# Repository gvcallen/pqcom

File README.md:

# PocketQube Satellite Communication System

## Overview
This repository holds code, datasheets, PCB schematics and other files related to the design and development of a PocketQube Satellite Communication System. This was done by Gary Allen in  partial fulfilment of the requirements of the module Project (E) 448 for the degree Baccalaureus in Engineering in the Department of Electrical and Electronic Engineering at the University of Stellenbosch, South Africa. PocketQubes are miniaturised satellites, and this project aimed to develop prototypes for the unit to be placed on the satellite, the ground station, and the PC interface. A video documenting the project can be found on YouTube at https://www.youtube.com/watch?v=bJcF6t-W-kM

## Code
This folder contains the relevant code for the project. Inside are 5 sub-folders. All embedded development was done using the *PlatformIO* extension on VS code, and all desktop GUI development was done using the *Qt* C++ library, both under WSL (Windows Subsystem for Linux). I highly recommend a linux install due to the ease of installation of the Qt libraries.
- ***gel*** is another Github repository created by myself containing the core embedded C++ classes used by the other projects. Even though it was developed solely for this project, I decided to make it an independent library so that it can be self-standing and potentially be used outside of the PocketQube project in the future.
- ***pqcu*** is the folder housing the code for the *PocketQube Communication Unit* i.e. the module to be placed on the PQ itself. It is very simple since it only "spits out" its GPS location via LoRa (i.e only downlink communication was implemented) however "gel" theoretically has an almost-ready foundation for dual-link communication (which was not implemented due to time constraints).
- ***pqgs*** contains code for the *PocketQube Ground Station*. This includes communication with the PQ unit, motor drive control, GPS tracking and serial control via a "TNC" (a.k.a a laptop connected via USB).
- ***pqui*** contains desktop GUI code to control the GS via USB and a PC. Theoretically, all control can be done via the terminal, however the GUI was implemented to make things slightly easier. It implements the SUNCQ protocol under ***Documents***.
- ***radiosonde_auto_rx*** was an extension of the project to receive data from a commercial Radiosonde via a software-defined radio (SDR). This is used by ***pqui***. Although the Radiosonde receiving is functional, it is currently implemented is a bit "messy", since a Python script is called and controlled from Qt, and this causes issues from time-to-time. If only "custom" communication is needed, this can be ignored.

## Other
The rest of the contents are relatively self-explanatory:
- ***datasheets*** contains various used (and not used) datasheets for ICs and modules.
- ***documents*** contains the SUNCQ protocol for PC to GS communication.
- ***images*** contains images taken throughout the project, such as during testing and final deployment.
- ***kicad*** contains the schematics developed for the PQ and the GS. The final Gerber files are also present in zip format. Note that some folders in here are old and need to be cleaned up.
- ***link-budget*** contains a pre-liminary link-budget done with free Python software.
- ***report*** contains the final report files for Latex. The final PDF is in the root of this folder.
- ***testing*** contains test results and data.

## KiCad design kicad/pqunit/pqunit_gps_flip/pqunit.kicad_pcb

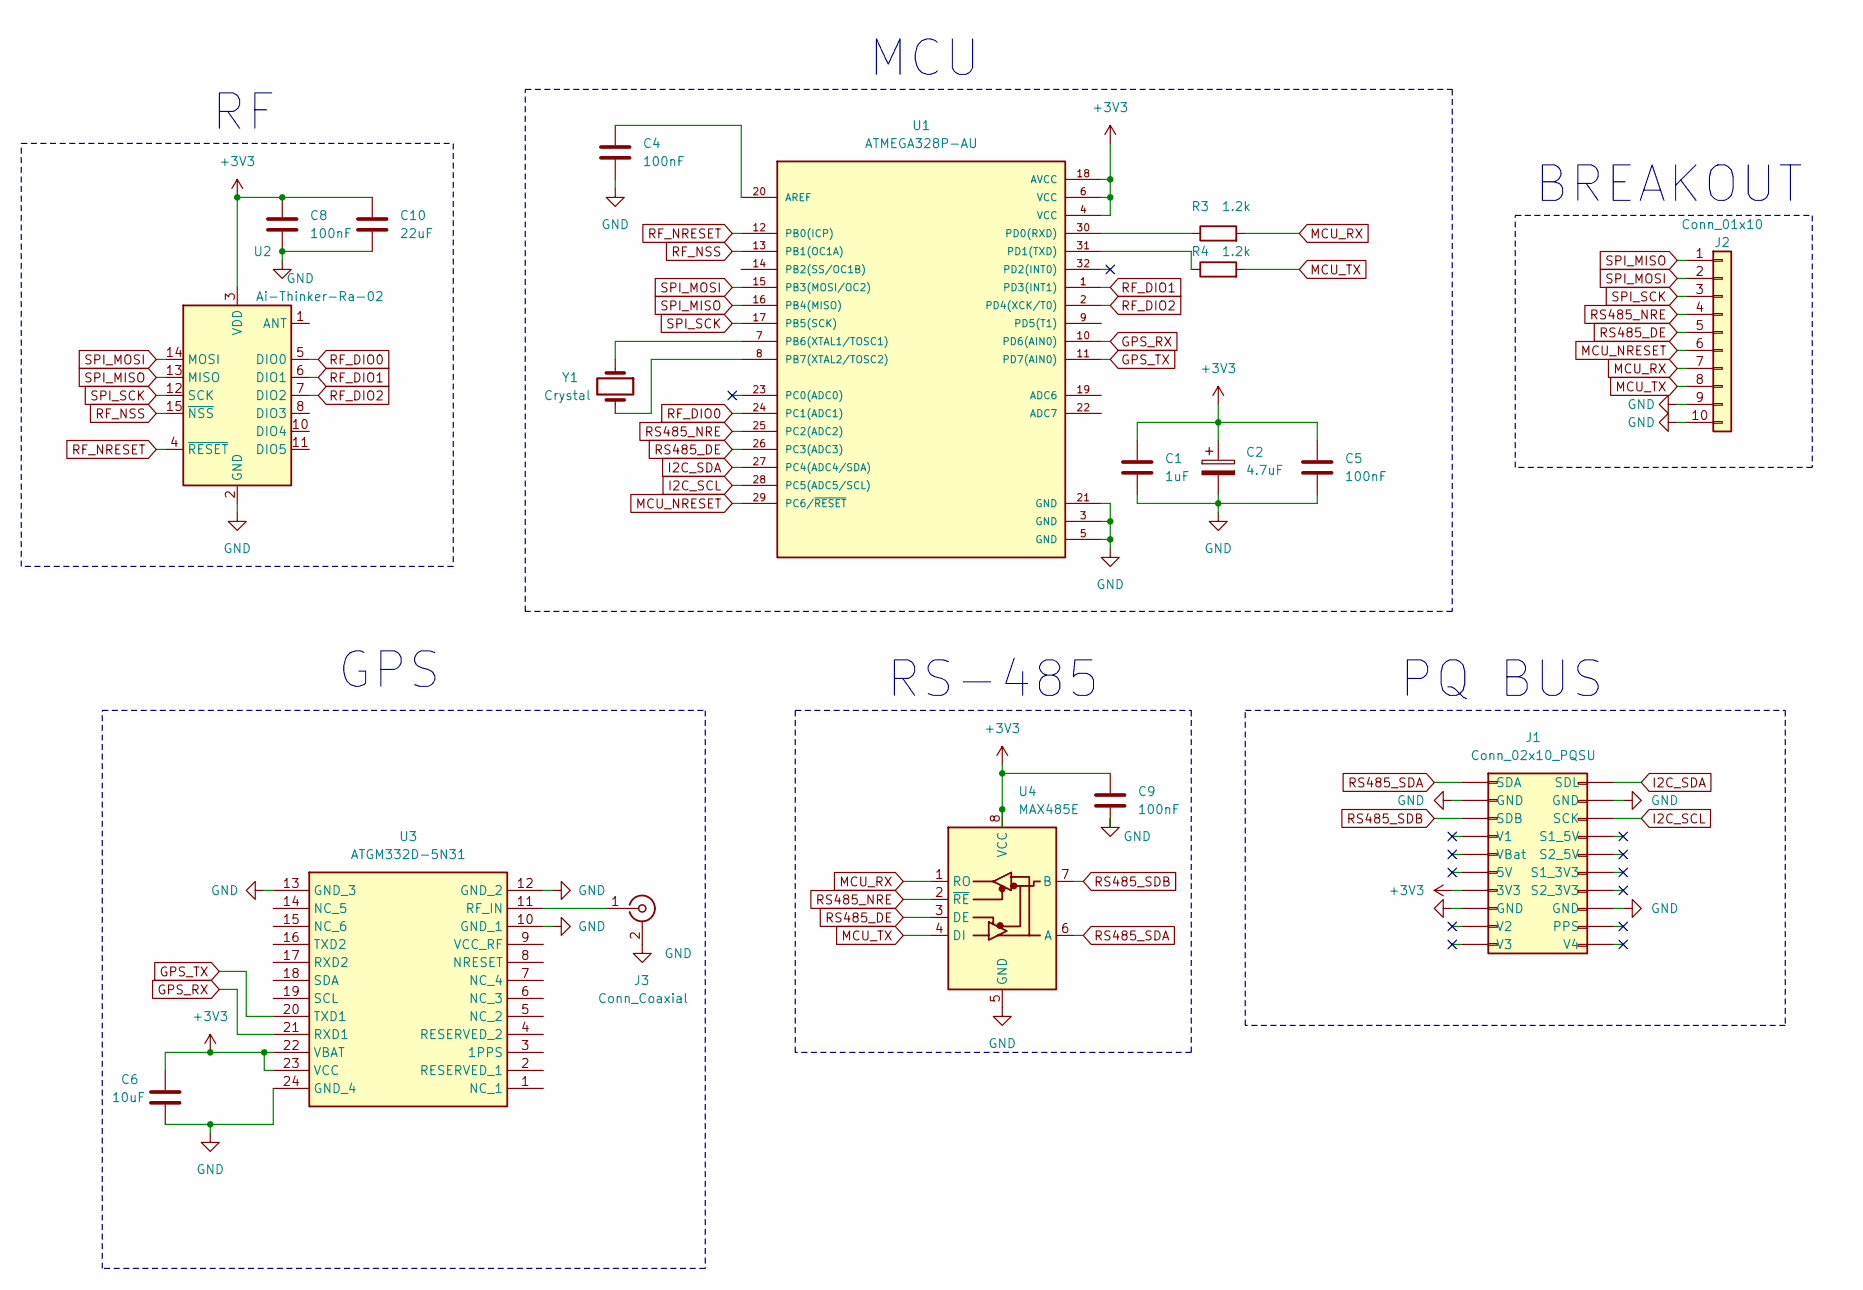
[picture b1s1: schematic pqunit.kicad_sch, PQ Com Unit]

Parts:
C1: 1uF; C_1206_3216Metric_Pad1.33x1.80mm_HandSolder
C2: 4.7uF; C_1206_3216Metric_Pad1.33x1.80mm_HandSolder
C4, C5, C8, C9: 100nF; C_0805_2012Metric_Pad1.18x1.45mm_HandSolder
C6: 10uF; C_1206_3216Metric_Pad1.33x1.80mm_HandSolder
C10: 22uF; C_1206_3216Metric_Pad1.33x1.80mm_HandSolder
J1: Conn_02x10_PQSU; PinSocket_2x10_P2.54mm_Vertical
J2: Conn_01x10; PinSocket_1x10_P2.54mm_Vertical
J3: Conn_Coaxial; U.FL_Molex_MCRF_73412-0110_Vertical
R3, R4: 1.2k; R_0805_2012Metric_Pad1.20x1.40mm_HandSolder
U1: ATMEGA328P-AU; TQFP-32_7x7mm_P0.8mm
U2: Ai-Thinker-Ra-02; Ai-Thinker-Ra-01-LoRa
U3: ATGM332D-5N31; ATGM332D5N31; Manufacturer_Part_Number ATGM332D-5N31
U4: MAX485E; SO08
Y1: Crystal; Crystal_SMD_HC49-SD

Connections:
+3V3: C1.1, C2.1, C5.1, C6.1, C8.1, C9.1, C10.1, J1.7 (3V3), U1.4 (VCC), U1.6 (VCC), U1.18 (AVCC), U2.3 (VDD), U3.22 (VBAT), U3.23 (VCC), U4.8 (VCC)
GND: C1.2, C2.2, C4.2, C5.2, C6.2, C8.2, C9.2, C10.2, J1.2 (GND), J1.8 (GND), J1.12 (GND), J1.18 (GND), J2.9, J2.10, J3.2 (Ext), U1.3 (GND), U1.5 (GND), U1.21 (GND), U2.2 (GND), U2.9 (GND), U2.16 (GND), U3.10 (GND_1), U3.12 (GND_2), U3.13 (GND_3), U3.24 (GND_4), U4.5 (GND)
GPS_RX: U1.10 (PD6(AIN0)), U3.21 (RXD1)
GPS_TX: U1.11 (PD7(AIN0)), U3.20 (TXD1)
I2C_SCL: J1.13 (SCK), U1.28 (PC5(ADC5/SCL))
I2C_SDA: J1.11 (SDL), U1.27 (PC4(ADC4/SDA))
MCU_NRESET: J2.6, U1.29 (PC6/~RESET)
MCU_RX: J2.7, R3.2, U4.1 (RO)
MCU_TX: J2.8, R4.2, U4.4 (DI)
unnamed: J3.1 (In), U3.11 (RF_IN)
unnamed: C4.1, U1.20 (AREF)
unnamed: U1.7 (PB6(XTAL1/TOSC1)), Y1.1
unnamed: U1.8 (PB7(XTAL2/TOSC2)), Y1.2
unnamed: R3.1, U1.30 (PD0(RXD))
unnamed: R4.1, U1.31 (PD1(TXD))
RF_DIO0: U1.24 (PC1(ADC1)), U2.5 (DIO0)
RF_DIO1: U1.1 (PD3(INT1)), U2.6 (DIO1)
RF_DIO2: U1.2 (PD4(XCK/T0)), U2.7 (DIO2)
RF_NRESET: U1.12 (PB0(ICP)), U2.4 (~RESET)
RF_NSS: U1.13 (PB1(OC1A)), U2.15 (~NSS)
RS485_DE: J2.5, U1.26 (PC3(ADC3)), U4.3 (DE)
RS485_NRE: J2.4, U1.25 (PC2(ADC2)), U4.2 (~RE)
RS485_SDA: J1.1 (SDA), U4.6 (A)
RS485_SDB: J1.3 (SDB), U4.7 (B)
SPI_MISO: J2.1, U1.16 (PB4(MISO)), U2.13 (MISO)
SPI_MOSI: J2.2, U1.15 (PB3(MOSI/OC2)), U2.14 (MOSI)
SPI_SCK: J2.3, U1.17 (PB5(SCK)), U2.12 (SCK)

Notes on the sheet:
PQ BUS
GPS
MCU
BREAKOUT
RS-485

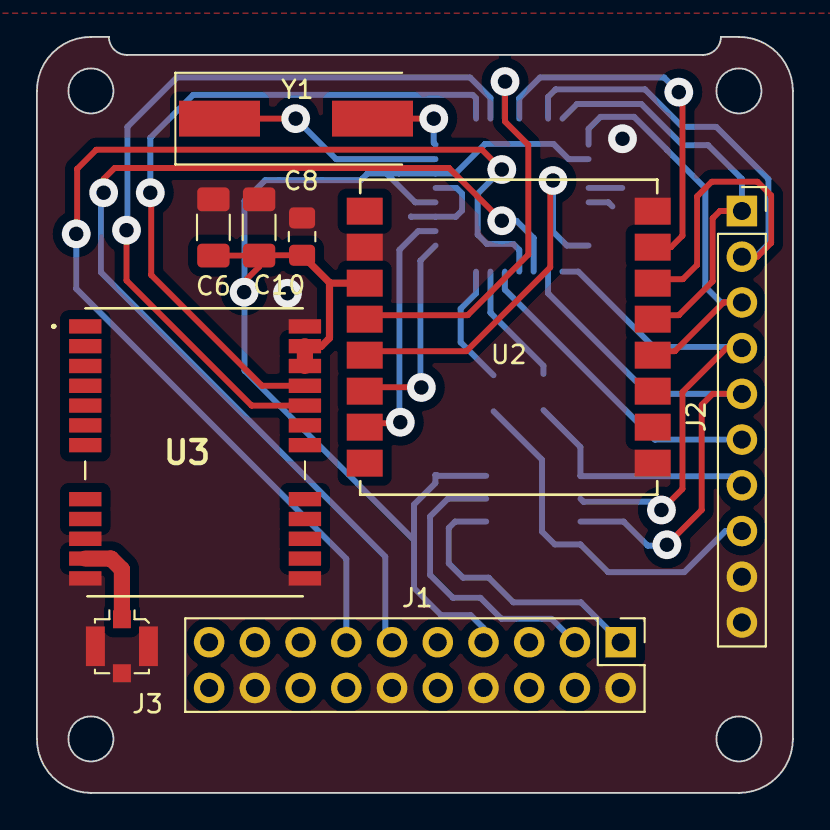
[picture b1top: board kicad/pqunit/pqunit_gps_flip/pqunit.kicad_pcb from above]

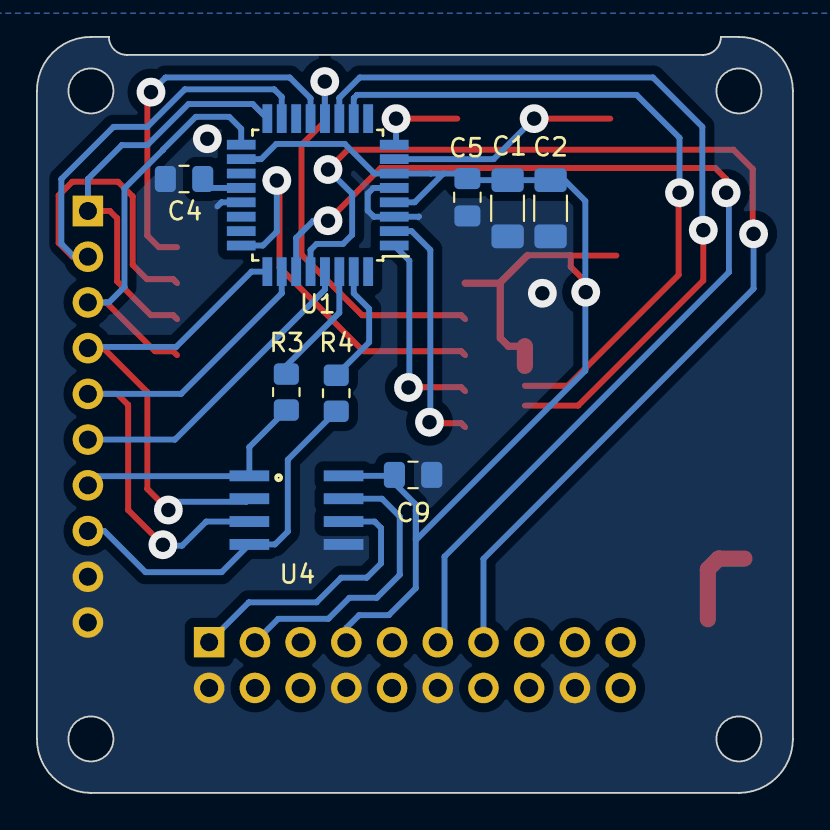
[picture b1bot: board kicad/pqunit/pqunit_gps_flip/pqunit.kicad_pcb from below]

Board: 2 copper layers, 42.0 x 42.0 mm, 18 parts (9 on the bottom side), 27 nets.

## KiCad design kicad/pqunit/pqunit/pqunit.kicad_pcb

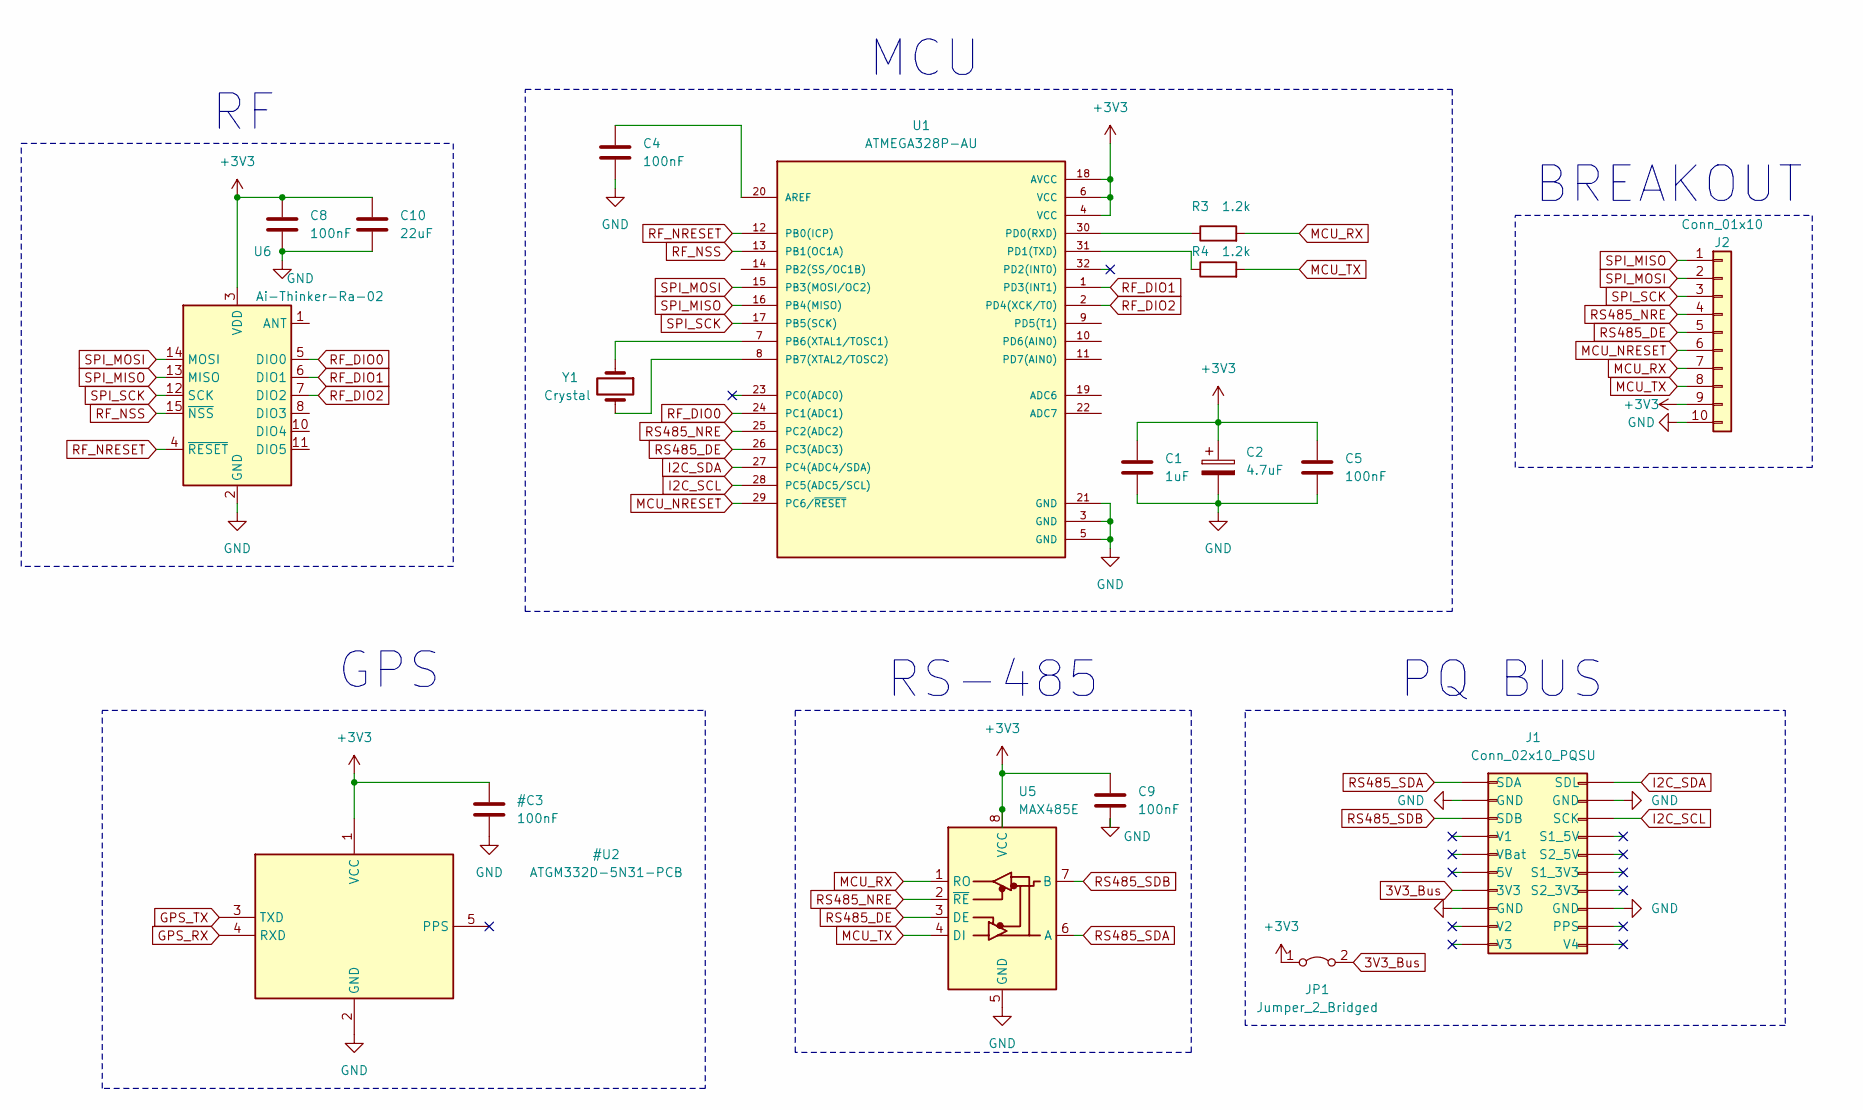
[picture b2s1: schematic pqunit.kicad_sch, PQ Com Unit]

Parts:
C1: 1uF; C_1206_3216Metric_Pad1.33x1.80mm_HandSolder
C2: 4.7uF; C_1206_3216Metric_Pad1.33x1.80mm_HandSolder
C4, C5, C8, C9: 100nF; C_0805_2012Metric_Pad1.18x1.45mm_HandSolder
C10: 22uF; C_1206_3216Metric_Pad1.33x1.80mm_HandSolder
J1: Conn_02x10_PQSU; PinSocket_2x10_P2.54mm_Vertical
J2: Conn_01x10; PinSocket_1x10_P2.54mm_Vertical
JP1: Jumper_2_Bridged; TestPoint_2Pads_Pitch2.54mm_Drill0.8mm
R3, R4: 1.2k; R_0805_2012Metric_Pad1.20x1.40mm_HandSolder
U1: ATMEGA328P-AU; TQFP-32_7x7mm_P0.8mm
U5: MAX485E; SO08
U6: Ai-Thinker-Ra-02; Ai-Thinker-Ra-01-LoRa
Y1: Crystal; Crystal_SMD_HC49-SD

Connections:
3V3_Bus: J1.7 (3V3), JP1.2 (B)
I2C_SCL: J1.13 (SCK), U1.28 (PC5(ADC5/SCL))
I2C_SDA: J1.11 (SDL), U1.27 (PC4(ADC4/SDA))
MCU_NRESET: J2.6, U1.29 (PC6/~RESET)
MCU_RX: J2.7, R3.2, U5.1 (RO)
MCU_TX: J2.8, R4.2, U5.4 (DI)
unnamed: C4.1, U1.20 (AREF)
unnamed: U1.7 (PB6(XTAL1/TOSC1)), Y1.1
unnamed: U1.8 (PB7(XTAL2/TOSC2)), Y1.2
unnamed: R3.1, U1.30 (PD0(RXD))
unnamed: R4.1, U1.31 (PD1(TXD))
RF_DIO0: U1.24 (PC1(ADC1)), U6.5 (DIO0)
RF_DIO1: U1.1 (PD3(INT1)), U6.6 (DIO1)
RF_DIO2: U1.2 (PD4(XCK/T0)), U6.7 (DIO2)
RF_NRESET: U1.12 (PB0(ICP)), U6.4 (~RESET)
RF_NSS: U1.13 (PB1(OC1A)), U6.15 (~NSS)
RS485_DE: J2.5, U1.26 (PC3(ADC3)), U5.3 (DE)
RS485_NRE: J2.4, U1.25 (PC2(ADC2)), U5.2 (~RE)
RS485_SDA: J1.1 (SDA), U5.6 (A)
RS485_SDB: J1.3 (SDB), U5.7 (B)
SPI_MISO: J2.1, U1.16 (PB4(MISO)), U6.13 (MISO)
SPI_MOSI: J2.2, U1.15 (PB3(MOSI/OC2)), U6.14 (MOSI)
SPI_SCK: J2.3, U1.17 (PB5(SCK)), U6.12 (SCK)

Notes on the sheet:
PQ BUS
GPS
MCU
BREAKOUT
RS-485

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
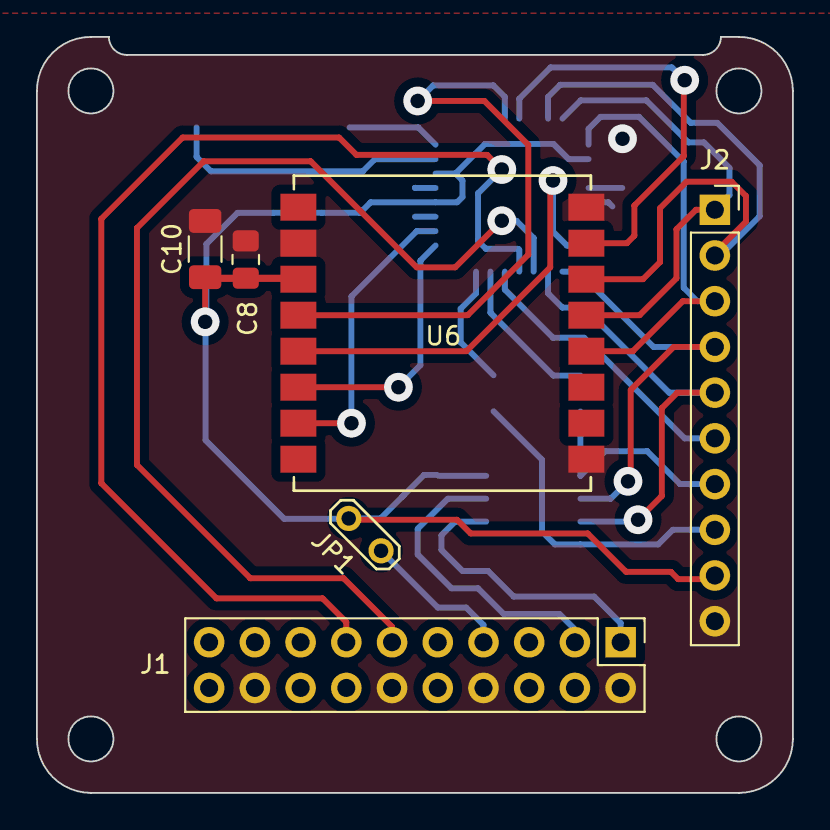
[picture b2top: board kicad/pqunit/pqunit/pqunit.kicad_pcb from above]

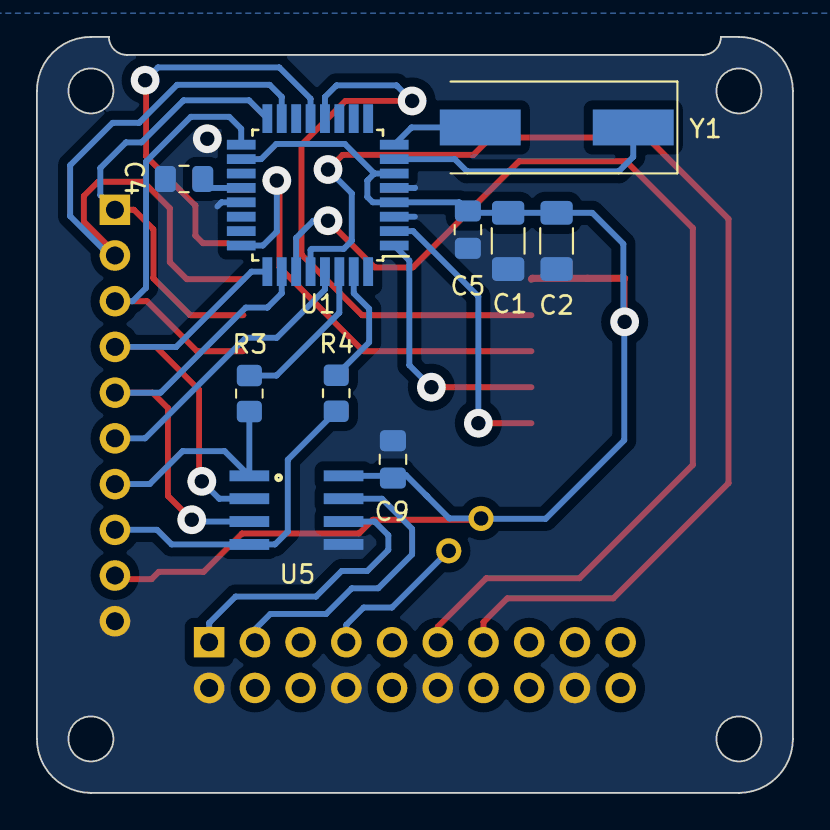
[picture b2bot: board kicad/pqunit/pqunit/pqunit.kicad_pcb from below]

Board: 2 copper layers, 42.0 x 42.0 mm, 16 parts (10 on the bottom side), 25 nets.

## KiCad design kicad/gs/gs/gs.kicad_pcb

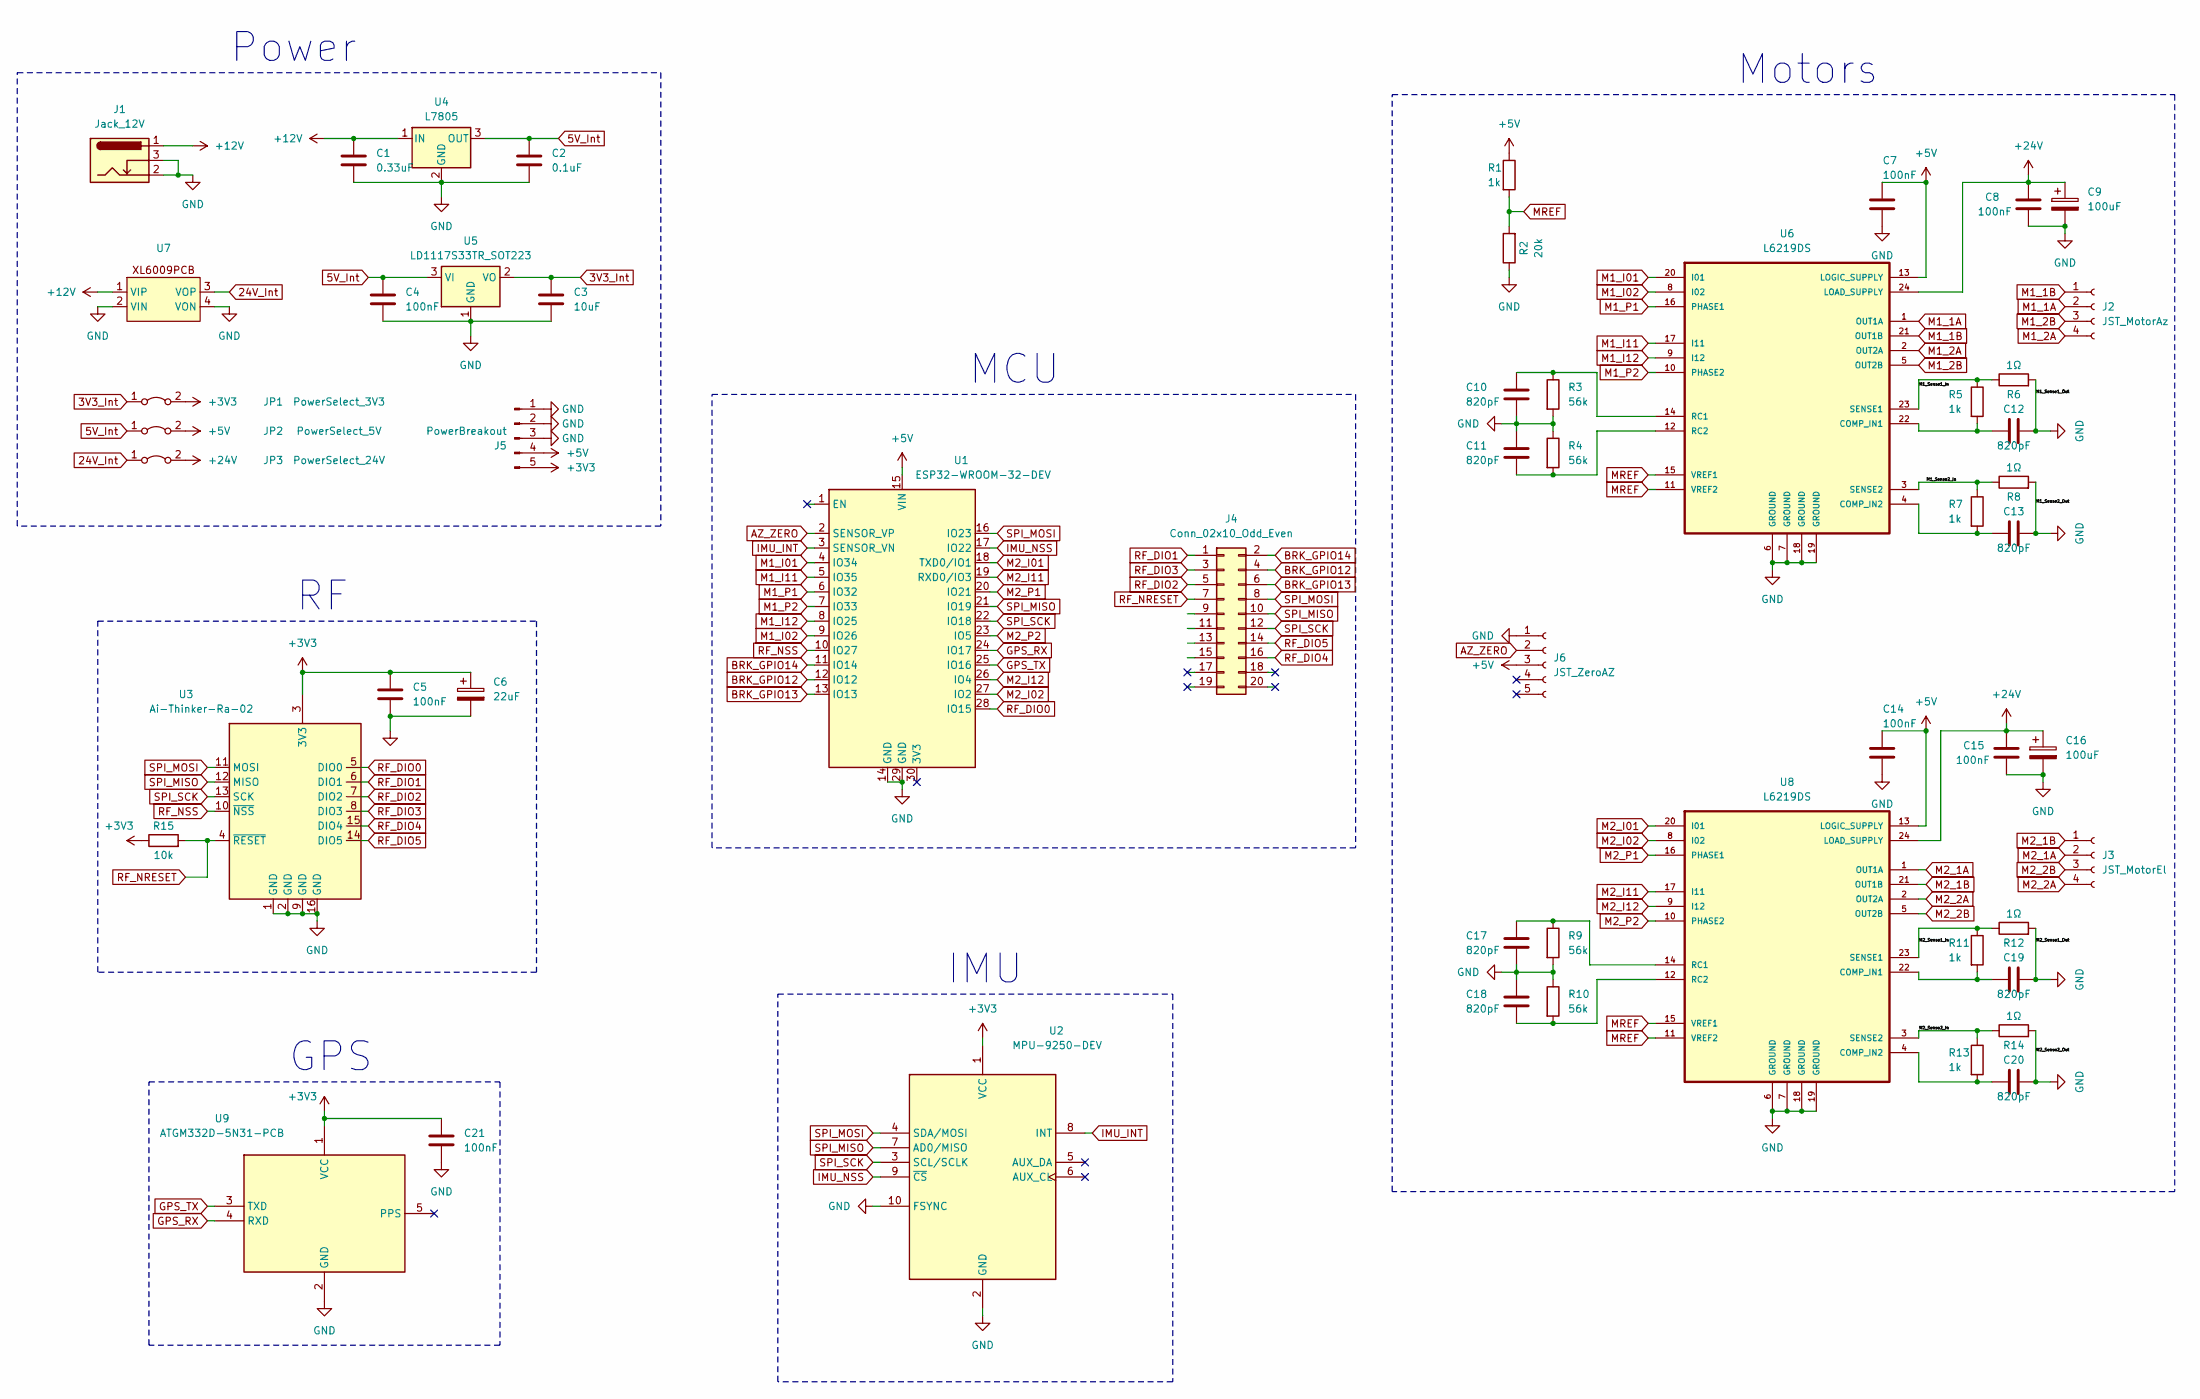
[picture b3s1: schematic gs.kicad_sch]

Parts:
C1: 0.33uF; C_Rect_L7.0mm_W4.5mm_P5.00mm
C2: 0.1uF; C_Rect_L7.0mm_W4.5mm_P5.00mm
C3: 10uF; C_Rect_L7.0mm_W4.5mm_P5.00mm
C4, C5, C7, C8, C14, C15, C21: 100nF; C_Rect_L7.0mm_W4.5mm_P5.00mm
C6: 22uF; CP_Radial_D5.0mm_P2.00mm
C9, C16: 100uF; CP_Radial_D5.0mm_P2.00mm
C10, C11, C12, C13, C17, C18, C19, C20: 820pF; C_Rect_L4.6mm_W2.0mm_P2.50mm_MKS02_FKP02
J1: Jack_12V; BarrelJack_Kycon_KLDX-0202-xC_Horizontal
J2: JST_MotorAz; JST_PH_B4B-PH-K_1x04_P2.00mm_Vertical
J3: JST_MotorEl; JST_PH_B4B-PH-K_1x04_P2.00mm_Vertical
J4: Conn_02x10_Odd_Even; PinHeader_2x10_P2.54mm_Vertical
J5: PowerBreakout; PinHeader_1x05_P2.54mm_Vertical
J6: JST_ZeroAZ; JST_PH_B5B-PH-K_1x05_P2.00mm_Vertical
JP1: PowerSelect_3V3; PinHeader_1x02_P2.54mm_Vertical
JP2: PowerSelect_5V; PinHeader_1x02_P2.54mm_Vertical
JP3: PowerSelect_24V; PinHeader_1x02_P2.54mm_Vertical
R1, R5, R7, R11, R13: 1k; R_Axial_DIN0207_L6.3mm_D2.5mm_P10.16mm_Horizontal
R2: 20k; R_Axial_DIN0207_L6.3mm_D2.5mm_P10.16mm_Horizontal
R3, R4, R9, R10: 56k; R_Axial_DIN0207_L6.3mm_D2.5mm_P10.16mm_Horizontal
R6, R8, R12, R14: 1Ω; R_Axial_DIN0207_L6.3mm_D2.5mm_P10.16mm_Horizontal
R15: 10k; R_Axial_DIN0207_L6.3mm_D2.5mm_P10.16mm_Horizontal
U1: ESP32-WROOM-32-DEV; ESP32-WROOM-32PCB
U2: MPU-9250-DEV; MPU-9250-PCB
U3: Ai-Thinker-Ra-02; RA-02-PCB
U4: L7805; TO-220-3_Horizontal_TabDown
U5: LD1117S33TR_SOT223; TO-220-3_Horizontal_TabDown
U6, U8: L6219DS; SOIC127P1030X265-24N
U7: XL6009PCB
U9: ATGM332D-5N31-PCB; Manufacturer_Part_Number ATGM332D-5N31

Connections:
3V3_Int: C3.1, JP1.1 (A), U5.2 (VO)
5V_Int: C2.1, C4.1, JP2.1 (A), U4.3 (OUT), U5.3 (VI)
24V_Int: JP3.1 (A), U7.3 (VOP)
+3V3: C5.1, C6.1, C21.1, J5.5, JP1.2 (B), R15.1, U2.1 (VCC), U3.3 (3V3), U9.1 (VCC)
+5V: C7.1, C14.1, J5.4, J6.3, JP2.2 (B), R1.1, U1.15 (VIN), U6.13 (LOGIC_SUPPLY), U8.13 (LOGIC_SUPPLY)
+12V: C1.1, J1.1, U4.1 (IN), U7.1 (VIP)
+24V: C8.1, C9.1, C15.1, C16.1, JP3.2 (B), U6.24 (LOAD_SUPPLY), U8.24 (LOAD_SUPPLY)
/M1_Sense1_In: R5.1, R6.1, U6.23 (SENSE1)
/M1_Sense2_In: R7.1, R8.1, U6.3 (SENSE2)
/M2_Sense1_In: R11.1, R12.1, U8.23 (SENSE1)
/M2_Sense2_In: R13.1, R14.1, U8.3 (SENSE2)
AZ_ZERO: J6.2, U1.2 (SENSOR_VP)
BRK_GPIO12: J4.4, U1.12 (IO12)
BRK_GPIO13: J4.6, U1.13 (IO13)
BRK_GPIO14: J4.2, U1.11 (IO14)
GND: C1.2, C2.2, C3.2, C4.2, C5.2, C6.2, C7.2, C8.2, C9.2, C10.2, C11.1, C12.1, C13.1, C14.2, C15.2, C16.2, C17.2, C18.1, C19.1, C20.1, C21.2, J1.2, J1.3, J5.1, J5.2, J5.3, J6.1, R2.1, R3.2, R4.1, R6.2, R8.2, R9.2, R10.1, R12.2, R14.2, U1.14 (GND), U1.29 (GND), U2.2 (GND), U2.10 (FSYNC), U3.1 (GND), U3.2 (GND), U3.9 (GND), U3.16 (GND), U4.2 (GND), U5.1 (GND), U6.6 (GROUND), U6.7 (GROUND), U6.18 (GROUND), U6.19 (GROUND), U7.2 (VIN), U7.4 (VON), U8.6 (GROUND), U8.7 (GROUND), U8.18 (GROUND), U8.19 (GROUND), U9.2 (GND)
GPS_RX: U1.24 (IO17), U9.4 (RXD)
GPS_TX: U1.25 (IO16), U9.3 (TXD)
IMU_INT: U1.3 (SENSOR_VN), U2.8 (INT)
IMU_NSS: U1.17 (IO22), U2.9 (~CS)
M1_1A: J2.2, U6.1 (OUT1A)
M1_1B: J2.1, U6.21 (OUT1B)
M1_2A: J2.4, U6.2 (OUT2A)
M1_2B: J2.3, U6.5 (OUT2B)
M1_I01: U1.4 (IO34), U6.20 (I01)
M1_I02: U1.9 (IO26), U6.8 (I02)
M1_I11: U1.5 (IO35), U6.17 (I11)
M1_I12: U1.8 (IO25), U6.9 (I12)
M1_P1: U1.6 (IO32), U6.16 (PHASE1)
M1_P2: U1.7 (IO33), U6.10 (PHASE2)
M2_1A: J3.2, U8.1 (OUT1A)
M2_1B: J3.1, U8.21 (OUT1B)
M2_2A: J3.4, U8.2 (OUT2A)
M2_2B: J3.3, U8.5 (OUT2B)
M2_I01: U1.18 (TXD0/IO1), U8.20 (I01)
M2_I02: U1.27 (IO2), U8.8 (I02)
M2_I11: U1.19 (RXD0/IO3), U8.17 (I11)
M2_I12: U1.26 (IO4), U8.9 (I12)
M2_P1: U1.20 (IO21), U8.16 (PHASE1)
M2_P2: U1.23 (IO5), U8.10 (PHASE2)
MREF: R1.2, R2.2, U6.11 (VREF2), U6.15 (VREF1), U8.11 (VREF2), U8.15 (VREF1)
unnamed: C12.2, R5.2, U6.22 (COMP_IN1)
unnamed: C13.2, R7.2, U6.4 (COMP_IN2)
unnamed: C10.1, R3.1, U6.14 (RC1)
unnamed: C11.2, R4.2, U6.12 (RC2)
unnamed: C19.2, R11.2, U8.22 (COMP_IN1)
unnamed: C20.2, R13.2, U8.4 (COMP_IN2)
unnamed: C17.1, R9.1, U8.14 (RC1)
unnamed: C18.2, R10.2, U8.12 (RC2)
RF_DIO0: U1.28 (IO15), U3.5 (DIO0)
RF_DIO1: J4.1, U3.6 (DIO1)
RF_DIO2: J4.5, U3.7 (DIO2)
RF_DIO3: J4.3, U3.8 (DIO3)
RF_DIO4: J4.16, U3.15 (DIO4)
RF_DIO5: J4.14, U3.14 (DIO5)
RF_NRESET: J4.7, R15.2, U3.4 (~RESET)
RF_NSS: U1.10 (IO27), U3.10 (~NSS)
SPI_MISO: J4.10, U1.21 (IO19), U2.7 (AD0/MISO), U3.12 (MISO)
SPI_MOSI: J4.8, U1.16 (IO23), U2.4 (SDA/MOSI), U3.11 (MOSI)
SPI_SCK: J4.12, U1.22 (IO18), U2.3 (SCL/SCLK), U3.13 (SCK)

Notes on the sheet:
Power
MCU
Motors
IMU
GPS

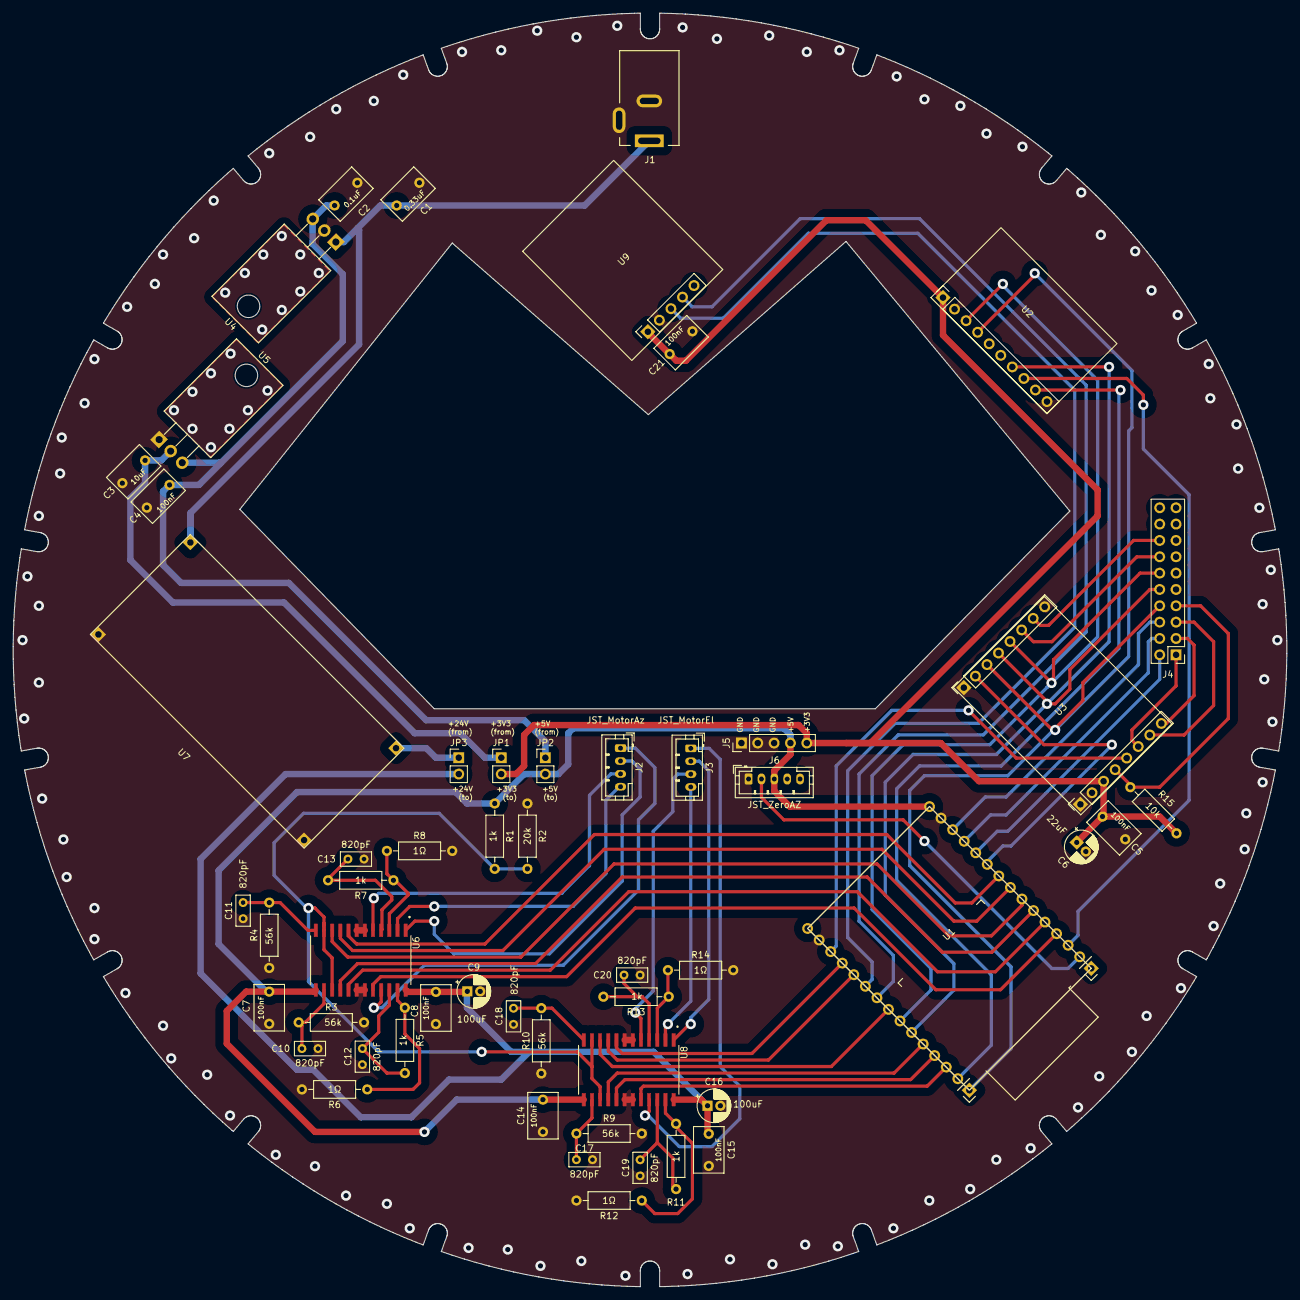
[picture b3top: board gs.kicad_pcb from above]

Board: 2 copper layers, 198.0 x 198.0 mm, 54 parts (0 on the bottom side), 60 nets.

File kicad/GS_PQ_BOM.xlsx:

# | Reference | Qty | Value | Footprint | Added
1 | C1 | 1 | 1uF | Capacitor_SMD:C_1206_3216Metric_Pad1.33x1.80mm_HandSolder | Y
2 | C2 | 1 | 4.7uF | Capacitor_SMD:C_1206_3216Metric_Pad1.33x1.80mm_HandSolder | YY
3 | C4, C5, C8, C9 | 4 | 100nF | Capacitor_SMD:C_0805_2012Metric_Pad1.18x1.45mm_HandSolder | Y
4 | C10 | 1 | 22uF | Capacitor_SMD:C_1206_3216Metric_Pad1.33x1.80mm_HandSolder
1 | C1 | 1 | 0.33uF | Capacitor_THT:C_Rect_L7.0mm_W4.5mm_P5.00mm
2 | C2 | 1 | 0.1uF | Capacitor_THT:C_Rect_L7.0mm_W4.5mm_P5.00mm
3 | C3 | 1 | 10uF | Capacitor_THT:C_Rect_L7.0mm_W4.5mm_P5.00mm
4 | C4, C5, C7, C8, C14, C15, C21 | 7 | 100nF | Capacitor_THT:C_Rect_L7.0mm_W4.5mm_P5.00mm
5 | C6 | 1 | 22uF | Capacitor_THT:CP_Radial_D5.0mm_P2.00mm
6 | C9, C16 | 2 | 100uF | Capacitor_THT:CP_Radial_D5.0mm_P2.00mm
7 | C10, C11, C12, C13, C17, C18, C19, C20 | 8 | 820pF | Capacitor_THT:C_Rect_L4.6mm_W2.0mm_P2.50mm_MKS02_FKP02
20 | R6, R8, R12, R14 | 4 | 1Ω1W | Resistor_THT:R_Axial_DIN0207_L6.3mm_D2.5mm_P10.16mm_Horizontal | Y
14 | JP1 | 4 | PowerSelect_3V3 | Connector_PinHeader_2.54mm:PinHeader_1x02_P2.54mm_Vertical | Y
11 | J4 | 1 | Conn_02x10_Odd_Even | Connector_PinHeader_2.54mm:PinHeader_2x10_P2.54mm_Vertical | Y
12 | J5 | 1 | PowerBreakout | Connector_PinHeader_2.54mm:PinHeader_1x05_P2.54mm_Vertical | Y
5 | J1 | 1 | Conn_02x10_PQSU | Connector_PinSocket_2.54mm:PinSocket_2x10_P2.54mm_Vertical | Y
6 | J2 | 1 | Conn_01x10 | Connector_PinSocket_2.54mm:PinSocket_1x10_P2.54mm_Vertical | Y
9 | J2 | 1 | JST_MotorAz | Connector_JST:JST_PH_B4B-PH-K_1x04_P2.00mm_Vertical
10 | J3 | 1 | JST_MotorEl | Connector_JST:JST_PH_B4B-PH-K_1x04_P2.00mm_Vertical
13 | J6 | 1 | JST_ZeroAZ | Connector_JST:JST_PH_B5B-PH-K_1x05_P2.00mm_Vertical
8 | U1 | 1 | ATMEGA328P-AU | Package_QFP:TQFP-32_7x7mm_P0.8mm | Y
9 | U5 | 1 | MAX485E | MAX485:SO08 | Y
10 | U6 | 1 | Ai-Thinker-Ra-02 | RF_Module:Ai-Thinker-Ra-01-LoRa | Y
11 | Y1 | 1 | Crystal | Crystal:Crystal_SMD_HC49-SD | Y
 |  |  |  | Battery | Y
 |  |  |  | Battery charger | Y

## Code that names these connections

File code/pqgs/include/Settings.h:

// Serial comms
#define BAUD_RATE                               115200
#define FLIGHT_PATH_MAX_SIZE                    5120

// Mount control
#define MOUNT_EL_ANGLE_MIN                      (35.0)
#define MOUNT_EL_ANGLE_MAX                      140.0
#define MOUNT_AZEL_RATIO                        -1.15
#define MOUNT_EL_START_NEAR_CUTOUT              true
#define MOUNT_EL_NUM_STEPS                      (200.0 * (92.0/20.0) * (140.0/80.0))
#define MOUNT_AZ_NUM_STEPS                      (200.0 * (60.0/15.0))

// Ground station control
#define GS_ESTIMATED_BEAMWIDTH                  60.0
#define GS_NUM_BEAMWIDTH_SCAN_SEGMENTS          4
#define GS_NUM_AZIMUTH_SCAN_SAMPLES             20
#define GS_SCAN_TIMEOUT                         120
#define GS_KNOWN_LOCATION_TRUST_TIMEOUT         60
#define GS_UPDATE_INTERVAL                      100
#define GS_MNORTH_DELTA_AZ                      -74.0
#define GS_MAP_PROJECTION_ORIGIN_LAT            -34.0
#define GS_MAP_PROJECTION_ORIGIN_LONG           19.0
#define GS_DEFAULT_LOCATION_LAT                 -33.9321
#define GS_DEFAULT_LOCATION_LONG                18.8602

// Pins
#define PIN_AZ_ZERO_SENSOR              36
#define PIN_AZ_IO1                      14
#define PIN_AZ_IO2                      26
#define PIN_AZ_I11                      12
#define PIN_AZ_I12                      25
#define PIN_AZ_PH1                      32
#define PIN_AZ_PH2                      33
#define PIN_EL_IO1                      0
#define PIN_EL_IO2                      2
#define PIN_EL_I11                      16
#define PIN_EL_I12                      4
#define PIN_EL_PH1                      21
#define PIN_EL_PH2                      5
#define PIN_RADIO_NSS                   27
#define PIN_RADIO_DIO0                  15
#define PIN_RADIO_RESET                 13
#define PIN_IMU_NSS                     22
#define PIN_GPS_RX                      39
#define PIN_GPS_TX                      16

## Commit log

2023-08-12 Added documents
2023-08-12 Deleted temp files
2023-08-12 Removed documents
2023-08-12 Removed documents folder
2023-08-20 Worked on schematics
2023-08-21 Finished first revision of PCBs
2023-08-30 Finished second revision of GS PCB
2023-09-01 2nd design of GS PCB
2023-09-01 Finished core of 2nd design of GS PCB
2023-09-01 Added details to GS PCB
2023-09-01 Finished GS PCB Rev 4
2023-09-01 Exported GS Rev 4 Gerbers
2023-09-01 Fixed GS PCB Rev 4 problems to be Rev 4.1
2023-09-01 Began PQUnit PCB Rev 2
2023-09-01 Fixed all PQUnit PCB Rev 2 errors
2023-09-03 Finished both PCB latest revisions
2023-09-14 Updated PQ PCB to include GPS and added initial PIO code
2023-09-16 Added abstractions in code and created GEL repo
2023-09-16 Added submodule
2023-09-16 Removed submodule
2023-09-28 Finished initial hardware testing
2023-09-28 Worked on report
2023-09-28 Finished system design in report
2023-09-28 Finished first half of detailed design
2023-09-28 Worked on report and added link budget script
2023-09-28 Started antenna design in report
2023-09-28 Added antenna design
2023-09-29 Finished antenna design
2023-09-29 Added helical antennap parameter table
2023-10-02 Worked on radio abstraction
2023-10-02 Prepared to rework submodule location
2023-10-02 Reworked links to gel library
2023-10-02 Removed etl as an independent dependency
2023-10-02 Made ETL a platform.io dependency
2023-10-02 Implemented ping-pong command-response
2023-10-02 Got ping-pong working smoothly
2023-10-03 Added broadcast and scan states
2023-10-03 Began work on application protocol
2023-10-03 Added support for LoRaLib
2023-10-04 Calibrated mount elevation and added angle control
2023-10-04 Calibrated mount azimuthal and added compensation movement
2023-10-06 Finished mount spherical coord abstraction
2023-10-10 Implemented initially GUI and PQGS TNC protocol
2023-10-11 Implemented initial code for flight path tracking
2023-10-12 Implemented initial GUI and tested serial protocol
2023-10-13 Implemented open loop tracking
2023-10-15 Added ISP
2023-10-15 Removed unnecessary zone identifiers
2023-10-17 Delta
2023-10-19 Collected data
2023-10-20 Ran further range tests and fixed PQ GPS
2023-10-21 Performed 4.6km measurement
2023-10-21 Performed GPS tracking test
2023-10-21 Started re-implementing brute force scanning
2023-10-21 Did 35km range test
2023-10-21 Test
2023-10-21 Did 50km range test
2023-10-22 Began reporting
2023-10-24 Finished initial draft except for testing
2023-10-24 Finished first draft
2023-10-24 Correct spelling errors of first draft
2023-10-27 Added radiosonde reverse engineering
2023-10-28 Bug fixes
2023-11-01 Updated report
2023-11-02 Found motor bug
2023-11-04 Did 122km range test
2023-11-04 Removed files
2023-11-06 Finished report
2024-02-28 Added final report
2024-02-28 Removed zone identifier
2024-02-28 Renamed report pdf
2024-02-28 Added readme and cleaned up some things
